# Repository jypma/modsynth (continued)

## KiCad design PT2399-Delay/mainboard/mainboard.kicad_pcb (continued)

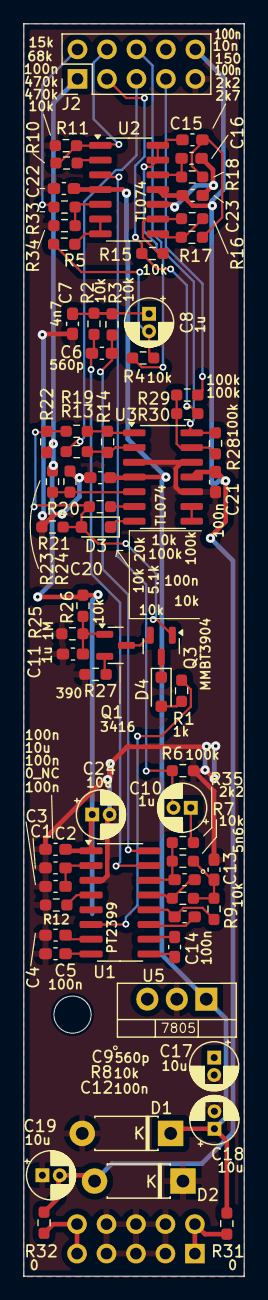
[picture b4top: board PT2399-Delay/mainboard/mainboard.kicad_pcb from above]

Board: 2 copper layers, 19.0 x 107.9 mm, 71 parts (1 on the bottom side), 51 nets.

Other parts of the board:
R6: 100k; R_0603_1608Metric_Pad0.98x0.95mm_HandSolder

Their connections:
/UNBUFFERED_WET: R6.1; also elsewhere on the board
GND: R6.2; also elsewhere on the board

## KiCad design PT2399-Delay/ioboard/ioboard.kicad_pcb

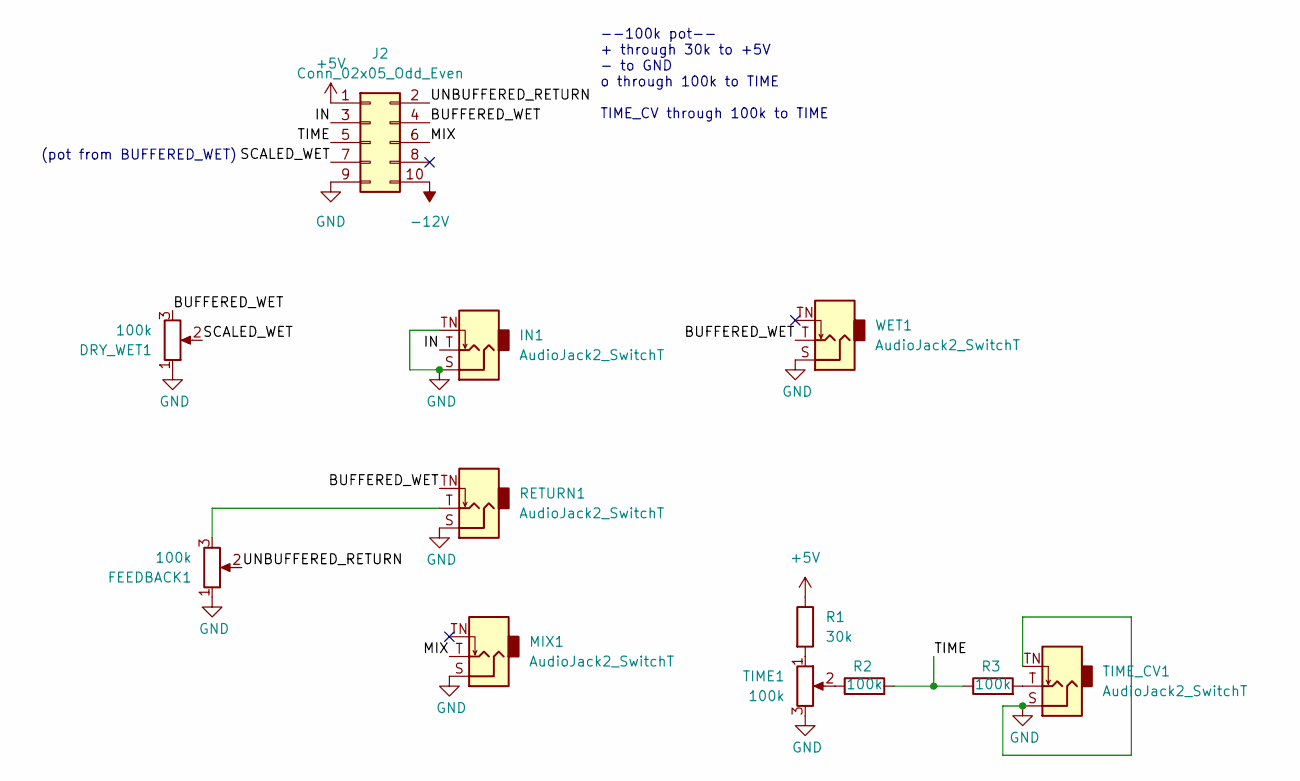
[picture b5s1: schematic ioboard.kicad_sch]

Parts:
DRY_WET1: 100k; Potentiometer_Alps_RK09K_Single_Vertical
FEEDBACK1: 100k; Potentiometer_Alps_RK09K_Single_Vertical
IN1: AudioJack2_SwitchT; Jack_3.5mm_QingPu_WQP-PJ398SM_Vertical_CircularHoles
J2: Conn_02x05_Odd_Even; PinHeader_2x05_P2.54mm_Vertical
MIX1: AudioJack2_SwitchT; Jack_3.5mm_QingPu_WQP-PJ398SM_Vertical_CircularHoles
R1: 30k; R_0603_1608Metric_Pad0.98x0.95mm_HandSolder
R2, R3: 100k; R_0603_1608Metric_Pad0.98x0.95mm_HandSolder
RETURN1: AudioJack2_SwitchT; Jack_3.5mm_QingPu_WQP-PJ398SM_Vertical_CircularHoles
TIME1: 100k; Potentiometer_Alps_RK09K_Single_Vertical
TIME_CV1: AudioJack2_SwitchT; Jack_3.5mm_QingPu_WQP-PJ398SM_Vertical_CircularHoles
WET1: AudioJack2_SwitchT; Jack_3.5mm_QingPu_WQP-PJ398SM_Vertical_CircularHoles

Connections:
+5V: J2.1, R1.1
-12V: J2.10
/BUFFERED_WET: DRY_WET1.3, J2.4, RETURN1.TN, WET1.T
/IN: IN1.T, J2.3
/MIX: J2.6, MIX1.T
/SCALED_WET: DRY_WET1.2, J2.7
/TIME: J2.5, R2.2, R3.1
/UNBUFFERED_RETURN: FEEDBACK1.2, J2.2
GND: DRY_WET1.1, FEEDBACK1.1, IN1.S, IN1.TN, J2.9, MIX1.S, RETURN1.S, TIME1.3, TIME_CV1.S, TIME_CV1.TN, WET1.S
unnamed: FEEDBACK1.3, RETURN1.T
unnamed: R1.2, TIME1.1
unnamed: R2.1, TIME1.2
unnamed: R3.2, TIME_CV1.T

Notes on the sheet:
(pot from BUFFERED_WET)
--100k pot-- + through 30k to +5V - to GND o through 100k to TIME TIME_CV through 100k to TIME

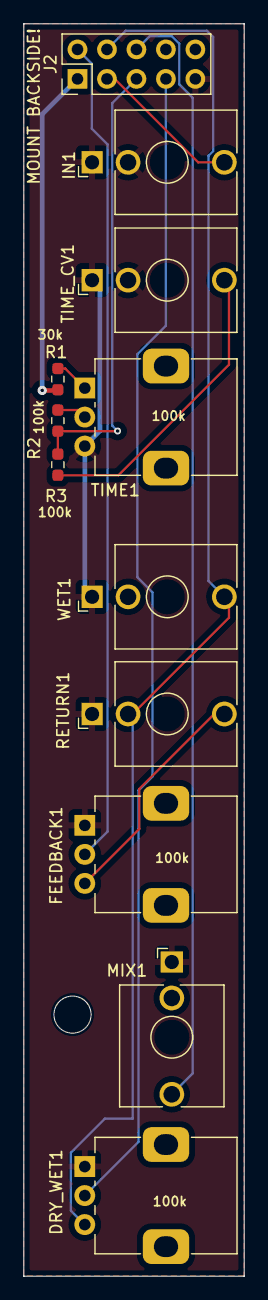
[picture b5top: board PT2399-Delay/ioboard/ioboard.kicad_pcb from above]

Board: 2 copper layers, 19.0 x 108.0 mm, 12 parts (0 on the bottom side), 12 nets.

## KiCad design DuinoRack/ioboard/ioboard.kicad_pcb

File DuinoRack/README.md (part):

# Design

- Screen
- 2 Encoders
- 2 bipolar CV inputs with Attenuverters and offset
  - On the MIDI variant, two attenuverters+offset are removed, to make space (only CV in for those).
CV inputs: attenuators plus offset, offset positive only
- 2 Gate inputs with trigger button.
- 2 CV outputs (from MPC4822, SPI)
- 2 Gate outputs (some I/O port)

# UI

Encoder 1: Select UI element
Encoder 2: Change value (immediate)

# Hardware
- Try a dual DIP/SOIC footprint for the ATMega328
- Run ATMega and MCP4822 off 5V, it'll be easier
- We might need a 5V precision reference for the ATMega's ADC (MCP4822 has internal reference)

## Notes for mainboard v1
- Remember: one TL074, one MCP6004!
- Zener diode is an inconvenient footprint. Just make it a normal zener THT.
- Value silkscreen is missing for C29 and C31 (both are 1 µF)
- Value silkscreen for ICs should be outside of the IC area
- No markings for power connector orientation
- Power connector is too close to the board edge
- MCP6004 isn't stable with the noise from the LEDs and screen. Add 2x 100nF (value needs to be tested) in parallel to R17 and R18.
- To reduce noise, C2 (AVCC cap for the ATMega) should be increased to 10uF (or perhaps in parallel to 100nF)
- C1 also to 10uF
- Replace the inrush resistors with links (test: 1Ohm ok?)
- 1k series resistors for OUTA (R10) and OUTB (R11) mess with the LEDs. Replace with 0k (see ioboard for replacement)
- In order for GATE OUT to reach -4V to +8V:
  + R49, R50 should be 15k (instead of 75k)
  + R47, R48 should be 20k (instead of 100k)
  + 2 extra 15k resistors from the common point of the above 2, to +5V (middle pin of the nearby voltage regulator), with modwire

## Notes for ioboard v1
- Value silkscreen is missing for R17, R18, R19 (should be 3.9k)
- Power and GND pins for screen are reversed, and should be cut and patched. Cause is that an earlier selected screen had these in reverse... From bottom view of  ioboard:
  - Rightmost screen pin should be VCC, scrape off solder mask of the actual VCC plane right below the pin, and blob connect.
  - Pin left of that should be GND, route to left button pin of rightmost encoder (still from bottom view of board). Unfortunately, the screen mislabeled GND pin was also the only route for GND to get onto the board. So, pin 15 of J4 (top right, bottom view) needs a jumper wire to that same GND encoder leg as well.
- GND plane wasn't regenerated properly. Use copper wire to connect several GND pins after assembly (see prototype). Combine with mod above.
- Attenuator pots are in reverse (bend pins 1 and 3 up, and swap with wires)
- LEDs for OUTA and OUTB should have 2k series resistor (THT) before going into GND hole.
- TODO Find a way to inject a 1k series resistor to the actual output jacks for OUTA and OUTB (might only be possible in next revision...)

# Software
- For high-detail modules (envelopes, LFO) try to update the MCP from a timer interrupt, so we can update the screen simultaneously? Perhaps only interrupt-driven WHILE we update the screen.
  - Otherwise, only update the screen after manual input, or on a low derivative...

# Potential modules

## ADSR

- 1 Gate input
- 4 variable inputs (can be virtual) for A,D,S,R (CV assignable)
   - positive only
   - not precise
- 1 CV output
- optional: 1 CV inverted output
- optional: 1 extra Gate input, 1 extra CV output (second envelope)

No looping (put LFO-like stuff in its own module)

Hints [here](https://github.com/baritonomarchetto/Programmable-Envelope-Generator/blob/main/ProgEnvGen_V2.ino)

## AR
(do we need this? Just have sustain at zero above)

- 1 Trigger input
- 2 CV inputs for A,D
- 1 CV output
- optional: 1 CV inverted output
- optional: 1 extra Gate input, 1 extra CV output (second envelope)

## LFO

- 1 input for tune (non-CV)
- 1 CV input (can be virtual) for freq
  - precise (if VCO frequency)
- optional: 1 Gate input for Freq.Counter / Tap tempo / Sync
- 1 menu input: Select wave shape
- 1 CV output
- optional: 1 CV output for extra wave, or 90 degrees offset wave
- toggle unipolar / bipolar

Hints [here](https://github.com/robertgallup/arduino-DualLFO). Need to check quality of the waveform using the MCP4822.

### To add:

- Offset, Attn (in addition to bidi? Instead of bidi?).
- Width (insert silence in middle of wave, where all waves are zero)
- Delay: Divide (2), Amount (%)... too complicated?
- Skip chance %
- EStep / ETrig (eucledean)
- Slop (earlier / later %,  but still in time?)

## LFO ADSR

Combine the two, applying the envelope to the LFO
- With reset on gate, or free-running
- Toggle unipolar / bipolar

## Pulse

- 1 input for tune (non-CV)
- 1 CV input (can be virtual) for freq
  - precise (if VCO frequency)
- optional: 1 Gate input for Freq.Counter / Tap Tempo / Sync
- 1 CV input (can be virtual): Pulse Width %
- 1 Gate output (or CV)
- optional: 3 extra outputs with dividers

## Clock divider

1 Gate input
N CV input + Gate output pairs, input sets divisor
Perhaps merge this with Pulse?

## Quantizer

Need to check if the incoming ADC is precise enough.

- 2 CV input
  - precise
- 2 Gate inputs for "hold"
- 2 CV outputs

## Sequencer

- encoder + 2 CV input for programming/recording. Modes for recording/setting CH1, CH2 or both
- Gate input advances the sequencer (consider internal clock as well)
- Add more later without adding UI elements

## MIDI

In:
- 2 CV outputs (note/bend and modulation)
- 1 Gate output
- 1 Clock output (selectable division)
- Selectable MIDI channel

Thru (electrical).

Out:
- 1 CV input (note & bend)
- 1 CV input (volume or mod)
- 1 Gate input
- Selectable MIDI channel
- Configurable to just send midi CV, no notes
- Configurable to mirror input (with 1-symbol delay), to allow chaining

Hints [here](https://note.com/solder_state/n/n17e028497eba) (incorporates pitch bend into the CV)
Original [midi2cv](https://github.com/elkayem/midi2cv)

## Random

- Noise with colors
- Random walk
- Sample & hold

## Chord quantizer mode

- Melody should pick different notes than just the chord

- Melody has fixed root note, scale is CV in, pitch is CV in

- Chord has root note (pitch) as CV in, chord type as CV in (scale is set to chromatic)
- Chord has 4 CV outputs
- Chord is stored as 16 bits (3x5 bit, for max 31 semitones offset).
- Use as mode for quantizer:
  + 2-channel note quantizer to one scale
  + 1-channel note quantizer with scale as CV-in
  + 1-channel chord quantizer with chord type as CV-in (selecting scale as chromatic, or anything that fits the sequencer before)

  Hence, for new Quantizer:
  - Mode: 2 notes, 1 note, chord
 - Clock input to sample and hold pitch, and rotate notes when in chord mode

 - Have quantizer create a gate when the pitch changes

# Simulation

## Output stage (TL074, -12..+12V)
[here](https://falstad.com/circuit/circuitjs.html?ctz=CQAgjCAMB0l3BWEBmATNA7AhAOBjVIAWfbEfc8ycgUwFowwAoIyAThADZUiVlOQGTjj4CIMAXTbQ2jMO2Q4wONpBxERMSKmTimAJS44RyYkZGoMqKDdbhr1R9AQHzKYW9aPb1Bg5swLoYIYNbICNZEaCgRNhB21v6BTADuXDwx1iFhsZBMAE5cCRlCFhnUofB5aaWigh6o5anpvGjU3LyNvNUtIF1F1P15hR19GRFl3SBEGPDNRGwC-RNj3UwA5tOLKGYLAsj8Aa574ES8J9vedkjeyQDy9SaHOHB1jgVbSxknYGc2pnNCid+idTFNCHMAPbgZBFWw4ThLJziFCo6iw5BMIA)
Try with 1% resistor and digital calibration, since it's far from the rails.

## Input stage (alt.2, MCP6004 protected, 0..5V)
- Not very useful, since pot controls offset, and needs to be in the middle for a bidirectional signal to make it through. Or is it? CV in would almost always be a
- Does the pot react the wrong way?
[here](https://falstad.com/circuit/circuitjs.html?ctz=CQAgjCAMB0l3BWEBmAHAJmgdgGzoRmACzICcpkORICkNNdCApgLRhgBQRkpIe1yZDhC5UKIeCjRhdGJHTIw8ZSvkh0HAEp9UY5JGo5d6rOijnu4M7KkItOvUYchuNupbbXzMO9oRgzZHR3IJRg8whLajdoOwB5ESdBYVQ4cRkoDgAnPnQBcP9A8LowVPhsvkt0PMSxaujwFQ4Ad1r1GtF0zNaqOnrc6n7IFoH2wxqg2RH+cBw6GaGOMCxqIiIxdjM1jdIzCFp4KXID1WUITSYAZwBLS4AXAEMAOwBjJntt8ACXdZBU7xcjABPgqCF2s3cVAhESaOTBZn6RFIwiGjWUH2RYxcmPwGXcdBYSBidgA5qNkAgzDMiGA8SN4ViFjVhq0GbT5jV2Zkcp9gmJeaYYeiyQKtrSTF5hgB7FyVCyoHDCJRSCB0ZAoczq5AcIA)
Build with 0.1% 100k and 180k resistors. Digital calibration after that.

## Input stage v2 (MCP6004, more accurate offset)
- Offset lands nicely in a middle range (maximum offset need not be calibrated)
- Calibrate 0V (offset to zero), and 4V (send precisely 4V on input)
[here](https://falstad.com/circuit/circuitjs.html?ctz=CQAgjCAMB0l3BWEBmAHAJmgdgGzoRmACzICcpkORICkNNdCApgLRhgBQRkpIOqqENzqpk6IXHBRoOKNMjpkYeCtUKQ6DgCUQWBOOT9d+lIbl1u4cXRvQE24+JLi9TquYkg2183YcJcFFRqIlJZNGo6CEsbX3sAeRBRJ0lUd2FzDgAnPgEg6gDw4LkwVBVs3UhqdDzkjTyo1Q4AdySxesE6jMgWyuq8-kEawR7WwY7cwQioXvH0dGo5ho4wLAKwcVXZBA2NBFkIZRV5SCQtJgBnAEsLgBcAQwA7AGMmf132cR3xMo9LJFiMHsORw+w0CxoNXBkXATR031M2xwdDEgM8LABcQ4AHNJkIwLJxkRfjZZmD5os8hSZjkEegsF9dsgzCjkPAKgjPjQPoEosgsOyAB4oKHoHhCUjIDS7ai7AAqAHsAA4AHQuAApIGqFQALAC2AEo1Tc1QAbBXNS63bUAMxtFyYtw4CqE4FkfNOI1gCH5WDA-P9oXQODC7tgcAgKJQcilyA4QA)

## Input stage v3 (offset now fixed, needs -9V)
[here](https://falstad.com/circuit/circuitjs.html?ctz=CQAgjCAMB0l3BWEBmAHAJmgdgGzoRmACzICcpkORICkNNdCApgLRhgBQRkpIOqqENzqpk6IXHBRoOKNMjpkYeCtUKQ6DgCUQWBOOT9d+lIbl1u4cXRvQE24+JLi9TquYkg2183YcJcFFRqIlJZNGo6CEsbX3sAeRBRJ0lUd2FzDgAnPgEg6gDw4LkwVBVs3UhqdDzkjTyo1Q4AdySxesE6jMgWyuq8-kEawR7WwY7cwQioXvH0dGo5ho4wLAKwcVXZBA2NBFkIZRV5SCQtJgBnAEsLgBcAQwA7AGMmf132cR3xMo8Yjxg9hyOH2GgWNBqYMi4DK8He4nQWC+ODoYliFjoLF46L8AHNJkIwLJxkRfjZZqD5os8lSZjlvuBdgytiVaHCAB4oSHoHhCUjIDS7ai7AAqAHsAA4AHQuAApIDKxQALAC2AEoZTcZQAbMXNS63RUAMyNFyYtw4YqE4FkUWQp0EWGgYDCyQCCAopH0Apg8AgqJQcgFyA4QA)

## Input stage v4 (offset now in the right direction, needs 8V)
[here](https://falstad.com/circuit/circuitjs.html?ctz=CQAgjCAMB0l3BWEBmAHAJmgdgGzoRmACzICcpkORICkNNdCApgLRhgBQRkpIOqqENzqpk6IXHBRoOKNMjpkYeCtUKQ6DgCUQWBOOT9d+lIbl1u4cXRvQE24+JLi9TquYkg2183YcIcOjRqIlJZYLkIS1kfGHsAeRBRJ0lUd2FzDgAnPgEUVGoEXHzqOnQsFWzdSGp0POSNPLplSoB3JLFGwQaMyA52itq8-kE6wT72ka7cwQiJmY10aimxqA4wLEKwcQ3ZBG2NAKkW+HlIJC0mAGcASyuAFwBDADsAYyZ-A-ZxffFUGzklhY4189hyOCO6CWNDqi1KGgq8E+4nKP0CKHQAIsWNBHAA5gsiGBZFMiP9MpNIdCVtC+gAPDGjHhCUjIDQHagHAAqAHsAA4AHSuAApIEKeQALAC2AEohXchQAbHmta73cUAMw1VyY936NC+B1+4GKfQJRVkGQtQk6Nn1ASCBRoxTmHB5QnAsmayHO3TOkAgQRQcjZyA4QA)

## -9V Reference
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
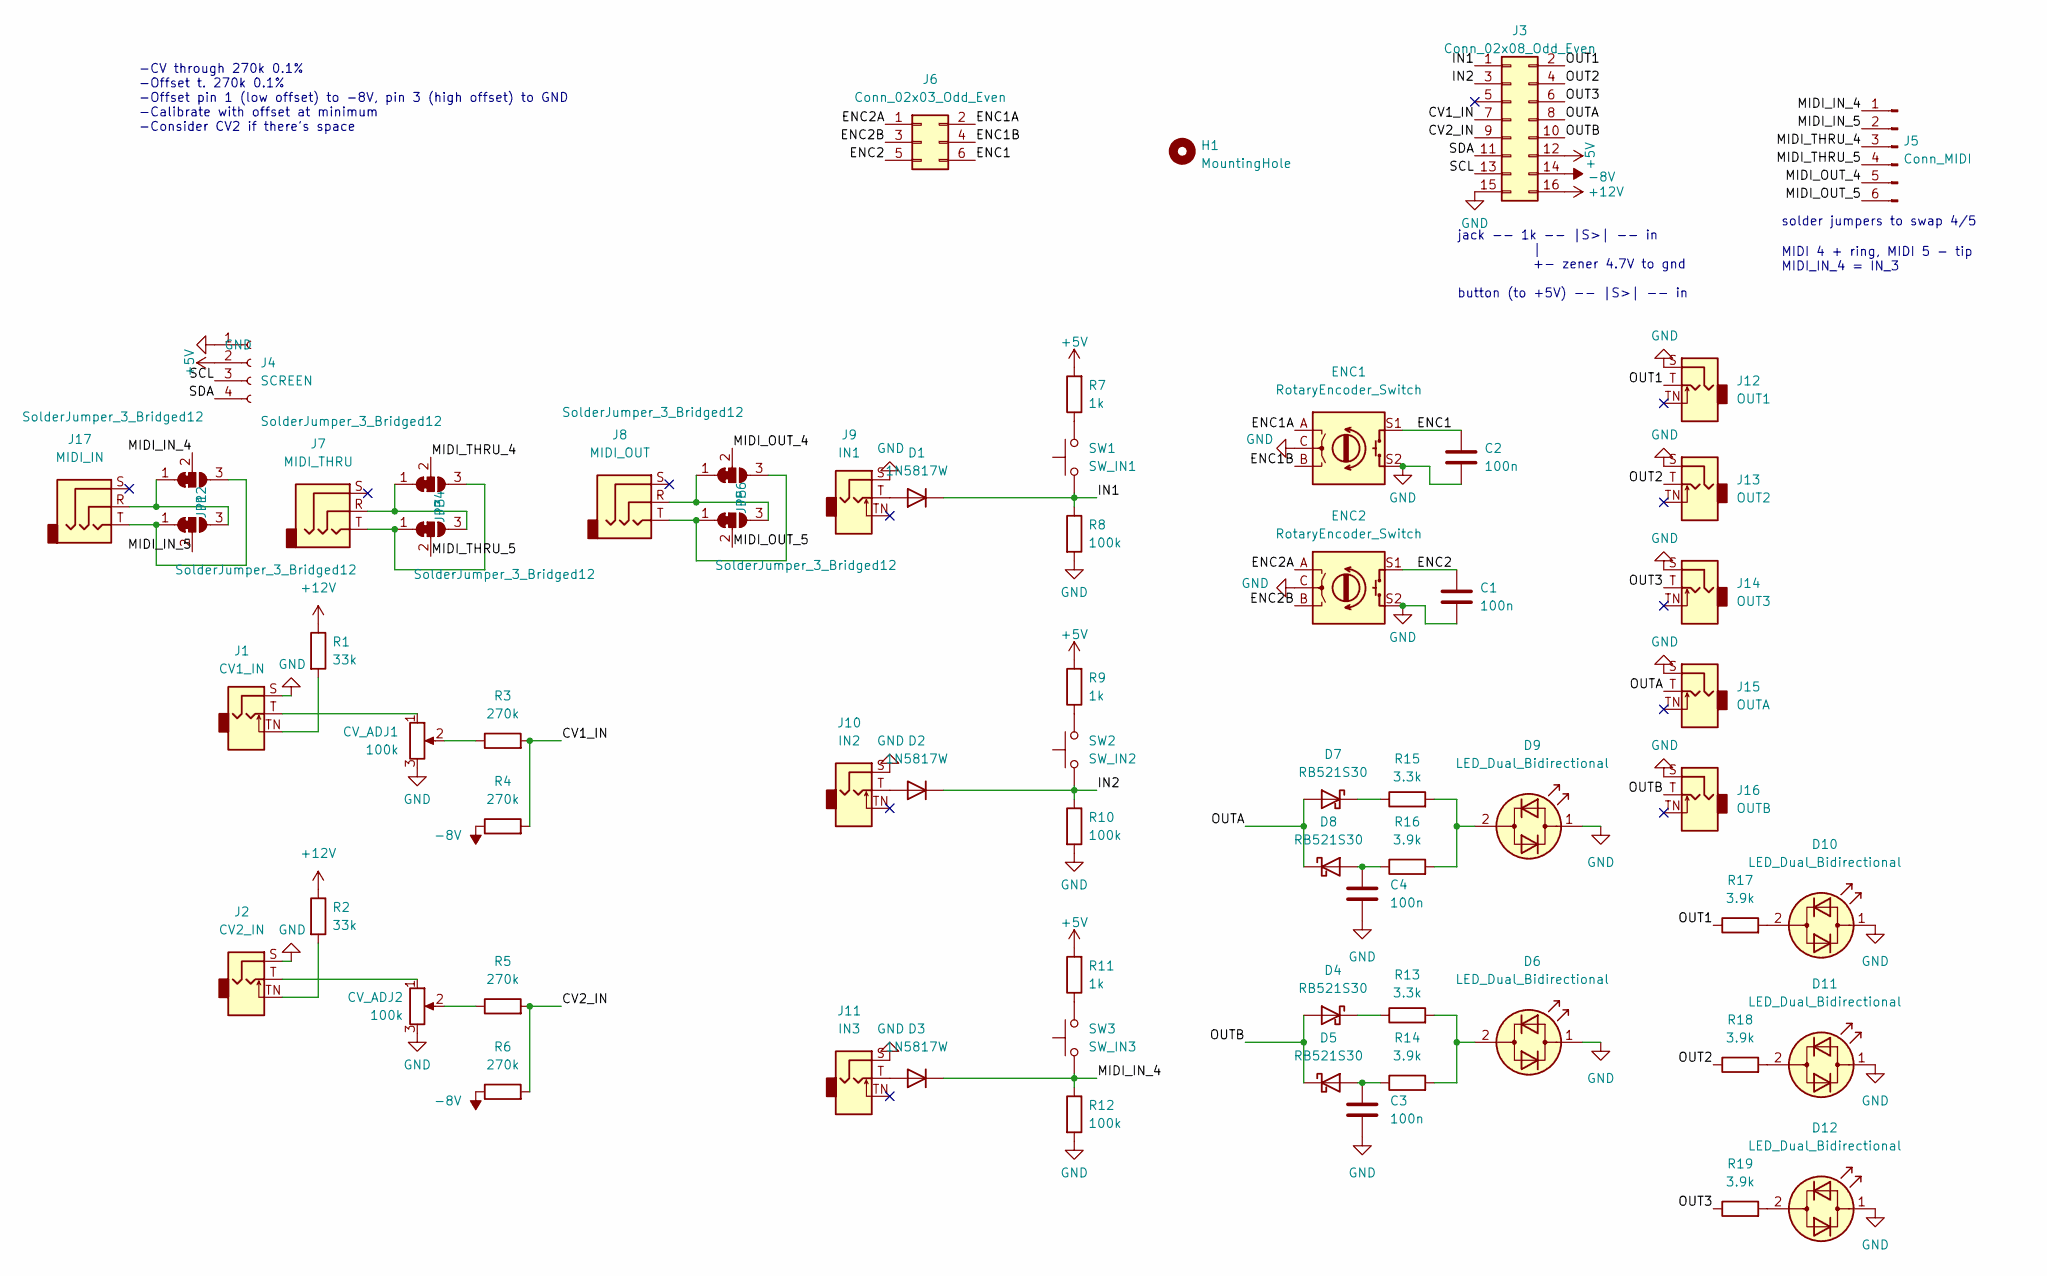
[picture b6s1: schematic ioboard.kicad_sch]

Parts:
C1, C2, C3, C4: 100n; C_0603_1608Metric_Pad1.08x0.95mm_HandSolder
CV_ADJ1, CV_ADJ2: 100k; Potentiometer_Alps_RK09K_Single_Vertical
D1, D2, D3: 1N5817W; D_SOD-123
D4, D5, D7, D8: RB521S30; D_SOD-523
D6, D9, D10, D11, D12: LED_Dual_Bidirectional; LED_D3.0mm
ENC1, ENC2: RotaryEncoder_Switch; RotaryEncoder_Alps_EC12E-Switch_Vertical_H20mm
H1: MountingHole; MountingHole_3.2mm_M3_DIN965
J1: CV1_IN; Jack_3.5mm_QingPu_WQP-PJ398SM_Vertical_CircularHoles
J2: CV2_IN; Jack_3.5mm_QingPu_WQP-PJ398SM_Vertical_CircularHoles
J3: Conn_02x08_Odd_Even; PinHeader_2x08_P2.54mm_Vertical
J4: SCREEN; PinSocket_1x04_P2.54mm_Vertical
J5: Conn_MIDI; PinHeader_1x06_P2.54mm_Vertical
J6: Conn_02x03_Odd_Even; PinHeader_2x03_P2.54mm_Vertical
J7: MIDI_THRU; Low-profile Minijack
J8: MIDI_OUT; Low-profile Minijack
J9: IN1; Jack_3.5mm_QingPu_WQP-PJ398SM_Vertical_CircularHoles
J10: IN2; Jack_3.5mm_QingPu_WQP-PJ398SM_Vertical_CircularHoles
J11: IN3; Jack_3.5mm_QingPu_WQP-PJ398SM_Vertical_CircularHoles
J12: OUT1; Jack_3.5mm_QingPu_WQP-PJ398SM_Vertical_CircularHoles
J13: OUT2; Jack_3.5mm_QingPu_WQP-PJ398SM_Vertical_CircularHoles
J14: OUT3; Jack_3.5mm_QingPu_WQP-PJ398SM_Vertical_CircularHoles
J15: OUTA; Jack_3.5mm_QingPu_WQP-PJ398SM_Vertical_CircularHoles
J16: OUTB; Jack_3.5mm_QingPu_WQP-PJ398SM_Vertical_CircularHoles
J17: MIDI_IN; Low-profile Minijack
JP1: SolderJumper_3_Bridged12
JP2, JP3, JP4, JP5, JP6: SolderJumper_3_Bridged12; SolderJumper-3_P1.3mm_Bridged12_RoundedPad1.0x1.5mm_NumberL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
R1, R2: 33k; R_0603_1608Metric_Pad0.98x0.95mm_HandSolder
R3, R4, R5, R6: 270k; R_0603_1608Metric_Pad0.98x0.95mm_HandSolder
R7, R9, R11: 1k; R_0603_1608Metric_Pad0.98x0.95mm_HandSolder
R8, R10, R12: 100k; R_0603_1608Metric_Pad0.98x0.95mm_HandSolder
R13, R15: 3.3k; R_0603_1608Metric_Pad0.98x0.95mm_HandSolder
R14, R16, R17, R18, R19: 3.9k; R_0603_1608Metric_Pad0.98x0.95mm_HandSolder
SW1: SW_IN1; SW_PUSH_6mm_H13mm
SW2: SW_IN2; SW_PUSH_6mm_H13mm
SW3: SW_IN3; SW_PUSH_6mm_H13mm

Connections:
+5V: J3.12, J4.2, R7.2, R9.2, R11.2
+12V: J3.16, R1.1, R2.1
-8V: J3.14, R4.1, R6.1
/CV1_IN: J3.7, R3.2, R4.2
/CV2_IN: J3.9, R5.2, R6.2
/ENC1: C2.1, ENC1.S1, J6.6
/ENC1A: ENC1.A, J6.2
/ENC1B: ENC1.B, J6.4
/ENC2: C1.1, ENC2.S1, J6.5
/ENC2A: ENC2.A, J6.1
/ENC2B: ENC2.B, J6.3
/IN1: D1.1 (K), J3.1, R8.1, SW1.1
/IN2: D2.1 (K), J3.3, R10.1, SW2.1
/MIDI_IN_4: D3.1 (K), J5.1, JP1.2 (C), R12.1, SW3.1
/MIDI_IN_5: J5.2, JP2.2 (C)
/MIDI_OUT_4: J5.5, JP5.2 (C)
/MIDI_OUT_5: J5.6, JP6.2 (C)
/MIDI_THRU_4: J5.3, JP3.2 (C)
/MIDI_THRU_5: J5.4, JP4.2 (C)
/OUT1: J3.2, J12.T, R17.1
/OUT2: J3.4, J13.T, R18.1
/OUT3: J3.6, J14.T, R19.1
/OUTA: D7.2 (A), D8.1 (K), J3.8, J15.T
/OUTB: D4.2 (A), D5.1 (K), J3.10, J16.T
/SCL: J3.13, J4.3
/SDA: J3.11, J4.4
GND: C1.2, C2.2, C3.2, C4.2, CV_ADJ1.3, CV_ADJ2.3, D6.1 (KA), D9.1 (KA), D10.1 (KA), D11.1 (KA), D12.1 (KA), ENC1.C, ENC1.S2, ENC2.C, ENC2.S2, J1.S, J2.S, J3.15, J4.1, J9.S, J10.S, J11.S, J12.S, J13.S, J14.S, J15.S, J16.S, R8.2, R10.2, R12.2
unnamed: C3.1, D5.2 (A), R14.1
unnamed: C4.1, D8.2 (A), R16.1
unnamed: CV_ADJ1.1, J1.T
unnamed: CV_ADJ1.2, R3.1
unnamed: CV_ADJ2.1, J2.T
unnamed: CV_ADJ2.2, R5.1
unnamed: D1.2 (A), J9.T
unnamed: D2.2 (A), J10.T
unnamed: D3.2 (A), J11.T
unnamed: D4.1 (K), R13.1
unnamed: D6.2 (AK), R13.2, R14.2
unnamed: D7.1 (K), R15.1
unnamed: D9.2 (AK), R15.2, R16.2
unnamed: D10.2 (AK), R17.2
unnamed: D11.2 (AK), R18.2
unnamed: D12.2 (AK), R19.2
unnamed: J1.TN, R1.2
unnamed: J2.TN, R2.2
unnamed: J7.R, JP3.1 (A), JP4.3 (B)
unnamed: J7.T, JP3.3 (B), JP4.1 (A)
unnamed: J8.R, JP5.1 (A), JP6.3 (B)
unnamed: J8.T, JP5.3 (B), JP6.1 (A)
unnamed: J17.R, JP1.1 (A), JP2.3 (B)
unnamed: J17.T, JP1.3 (B), JP2.1 (A)
unnamed: R7.1, SW1.2
unnamed: R9.1, SW2.2
unnamed: R11.1, SW3.2

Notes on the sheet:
solder jumpers to swap 4/5
jack -- 1k -- |S>| -- in | +- zener 4.7V to gnd button (to +5V) -- |S>| -- in
-CV through 270k 0.1% -Offset t. 270k 0.1% -Offset pin 1 (low offset) to -8V, pin 3 (high offset) to GND -Calibrate with offset at minimum -Consider CV2 if there's space
MIDI 4 + ring, MIDI 5 - tip MIDI_IN_4 = IN_3

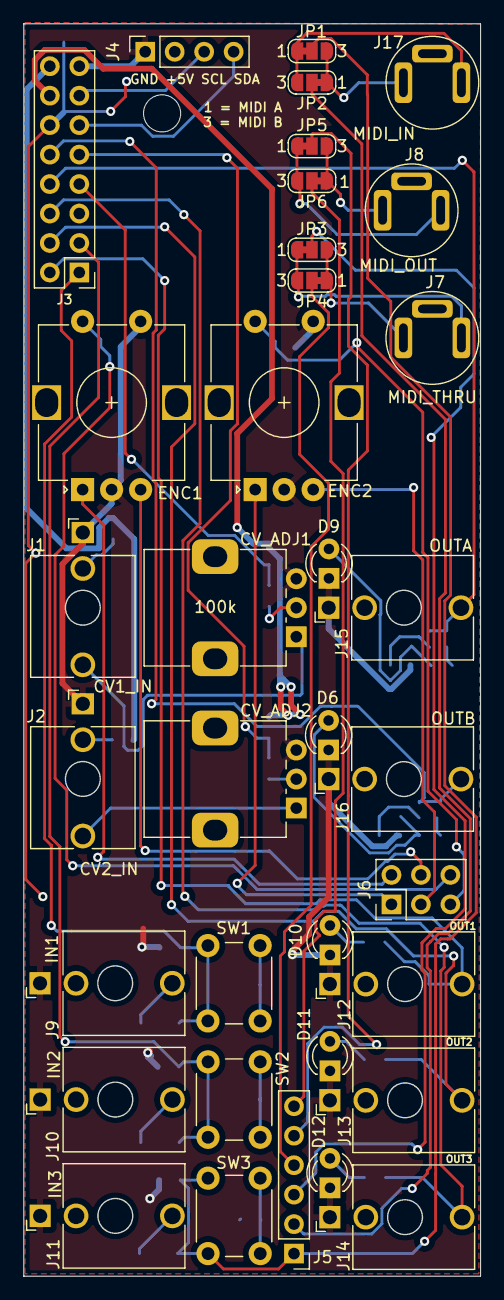
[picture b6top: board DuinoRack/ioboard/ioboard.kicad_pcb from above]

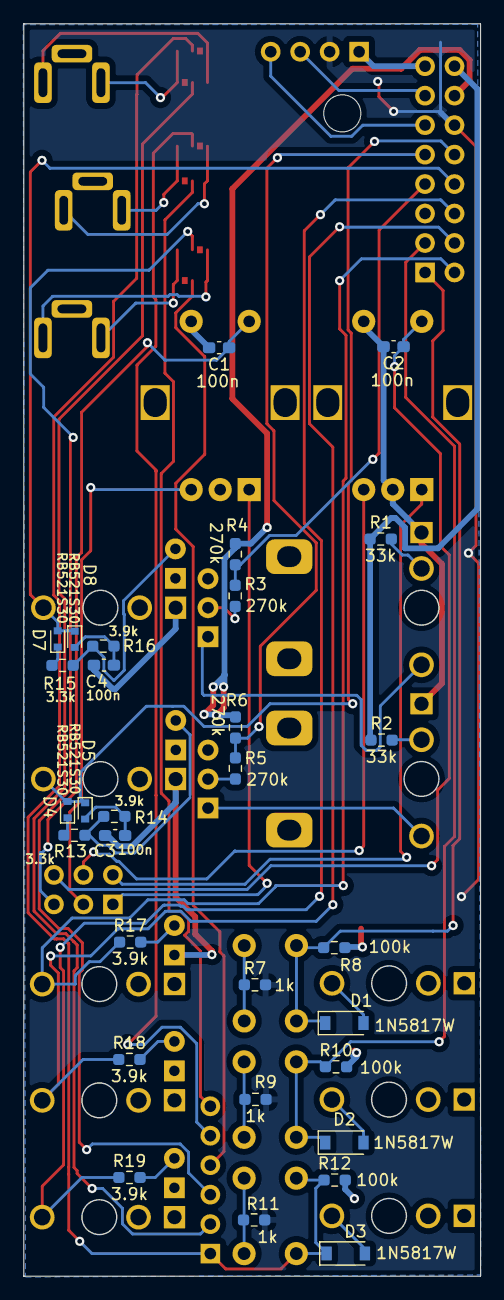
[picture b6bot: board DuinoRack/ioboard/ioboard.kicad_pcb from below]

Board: 2 copper layers, 39.4 x 107.9 mm, 66 parts (30 on the bottom side), 54 nets.

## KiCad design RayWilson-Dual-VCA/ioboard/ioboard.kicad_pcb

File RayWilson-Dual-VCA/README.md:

# Ray Wilson Dual VCA

Source: [RayWilson-Dual-VCA](https://github.com/gerb-ster/RayWilson-Dual-VCA/) on Github

The following modifications were made by me:

- Converted schematics and board to Kicad
- Added component values to silk screen
- Added a PCB faceplate in Kicad
- Split up into separate main and io board

## Main board

### Schematic

### PCB

## IO board

### Schematic

### PCB

## Face plate

# Calibration

See also the original instructions [here](http://musicfromouterspace.com/index.php?MAINTAB=SYNTHDIY&VPW=1910&VPH=716)

TODO: Look up the right R designations here

    Disconnect any inputs or CV from the VCA.
    Set the Log/Linear switch to Linear.
    Connect the black lead of a DVM set to volt range to ground.
    Connect the red lead of a DVM set to volt range to the wiper of BIAS control on panel.
    Adjust BIAS until you are as close as possible to 0 volts on the wiper.
    Disconnect the red lead.
    Connect the red lead of a DVM set to millivolt range to the output of the VCA.
    Adjust trimmer R1/R2 (100k) so that you have 0 volts on the output of the VCA.
    Disconnect the meter.
    Connect a 100 hz +/-5 volt square wave output from a signal generator to one of the CV inputs of the VCA.
    Observe the output of the VCA with an oscilloscope (adjust the scope as needed).
    The control voltage should appear on the output but at a much lower amplitude.
    Adjust trimmer R3/R4 (2k) to minimize the control voltage feedthrough.
       -> There's a balance here: If you do minimize the feedthrough, the VCA's max output level will be significantly attenuated (with a +5V signal). I leave it such that I still have ~80% of incoming oscillator signals left.
    If you have no oscilloscope you can listen to the output and adjust for least CV feedthrough.

# TODO

- Values are missing on I/O and main board
- IC value can't be read on main board
- No mounting holes in main and I/O board (there's space in the bottom for manual drilling)
- Holes for switches on I/O board aren't big enough. Drill is possible, but use lots of solder for channel2, since traces connect at the top (and drilling ruins the through-hole connection).
- SMD footprints are missing pin 1 circle

# Simulation

https://www.falstad.com/circuit/circuitjs.html?ctz=CQAgjCAMB0l3BWcMBMcUHYMGZIA4UA2ATmIxAUgoqoQFMBaMMAKACUQU89xiVOUAFl78qENJ2hIUUqFCktBkYiAwJ+2dSDyCem-hBiE5MSCmxh4V62c4sA7qq3ZsxjBJfHI7bXBDYJPD8uHioqJXBREwUOIKpsHV9wsC85CKYosIUAJyd+FARjHR4C1LQ4BzzOQqrPKEri6qLdfy1vXLV+QUJhPACQbuEqcvaqwZBCdwGeuUsrH0mumcWB-rCBsUz5BBYAc21+8b6u4lTvR07-Qh5L8e8OSwiUIWQnmvX0sC2YHYfIGsulgBEg+mxM20UyhApAMfGQ3BE4HkxiYP0gYE0CAQGLwCAwfSQpnMhhYuRh4AwzR4YEpchGDRapW0LRpXlJ0LhzAM+GpX1m1kq5K5HIMtPO8OpnJ54D54vJaB45NwQz2yCmyrVGlcJh8xD5Gr1+SmoMi4J+7KVkGEhv8Vv58zJcI1lnVdvCGHFlgRYE5KBSiNGX39PoMfuMITkuHg7KD4e9Yf8iWG8weCYSwljA39JoyZoUSm5L0INWY2uLxkMAB0AM6QGtKGsMYg1uu1luyVuthvV5ttvs-KA1sCNjDQQRkbCCbFW5SQDDdduUSnMQgoUgF1eCIdwGsAEzoADMAIYAVwANgAXQfV4fVhho5cpNfEDdCRdzzTXSDF7iFUjb1t92Pc8r1bW9OykD9CiCH9cRIXs5j3Q9T0va9bwYPBYCEPA9TIQpNHRcCxzwSk8B6BBiASK1nitACkOA1CwMbTD0UEfFXDxMAKMIDF23HIEKO-a5sDUXE6OrICUNAxsiN0UiwEEDEvkIXAFMbGA5MEIgeK+BJrhwQhxMkkDryYFt1OI+dtK5PSSNcIzkJM1szJvQhYHHDAXzgMAdC4Yg8AsuTrgUpSiFUrcbx3CTHMYmS+L1f58DxfA+BXQLiDnU5IHTNi+gIQzIsAmLpLvcD0sywhsp0XKEiIByGJKly3JIsw8BpXQLFwMiEHSoEko9HC-RSeqpLQ8za0srSuKCIRThwHrCvo0amLvDSSMmFTKIQLTBEU+c+JIqaEBm8dJk0EanKHRtiGgGlMBwWrNCwXQDspSlsC2na9oixDooasb+1gdEehXdFSACLgKJQC7Ypvcb7yBu6CBIx50UxOrFr+qTKi5WhdplCQI09L5hnjf0iZYESxBJih8dxiYXkMeoOAMhnhHLNnZltWg8x2DoyxeY5ObEAV2oOfhN3F1QJHEeBthANg6GrABLasLyPAA7ABjOh2SF9wqCFtrUi47x9iN-0jZaMIGR4FZGkl8UHcF-pHZxsx2cFlo3f2Swi29D3pfWYmyxLDE3DaGNw6qIEI6iNiU1eMRKqTyJQjSMFg5yGVtUBcx+Eud1o19-OY9L-EhnqXJSzjnOqTpGwWDF2PmWpOd+BtCA5jlgdFZVtXNZ1nwW8aEfswz00s9+ZAak7-5jBfSvwioXMp-dqZuGp7VN-qRwa+0II69b+olE2ZYSwCO2SwB1FoFxP0uB6BJKHD98PZ5EIfUECwYZK9DmGgPoVwxB1BnQVO2HipxLCkGOFgdQv9wA4yIOzMOoc2QPEvhMCIGIuATHwOCbB3wFB70wSsBS+CViBiUHbKY5CbhtAGB6e44BqEx1YRXAhK9ZTRD5iwihtDKDs2NMgCoAB5cAgiJgCLLMI7w4jGhMh3kyG2Ys6gKWEHUIQYgaA9yBkgAAwgANUqPoREEYQz1H2JoiImjZHskUhWfGDj-DahFvMRwainHBnxqMZxmiER1DccXTgATtQRlcOncUfjtTOLuPY-04wmR3BEdGMWWiszhgiNiAwKT5BoGwCAAAQsrI81YfDpOcek9MnDJ48PKVkvk6TtpLw2CAVedSLgeBif6QJLBxF+09hmQOeIzh9MiMGX0wYU42wAPZyBmAUr4a5hhSA+t-Y6kM4CVRUKYbydJVDkG8HMlwWDZjPBwvIeAhggasREh6VwXogx+iRFqfwLA5k8VOcvfy1AYDiEQXM2kMxNjLMuclOcc4PTmBIJ5LwNyICLJYEAA

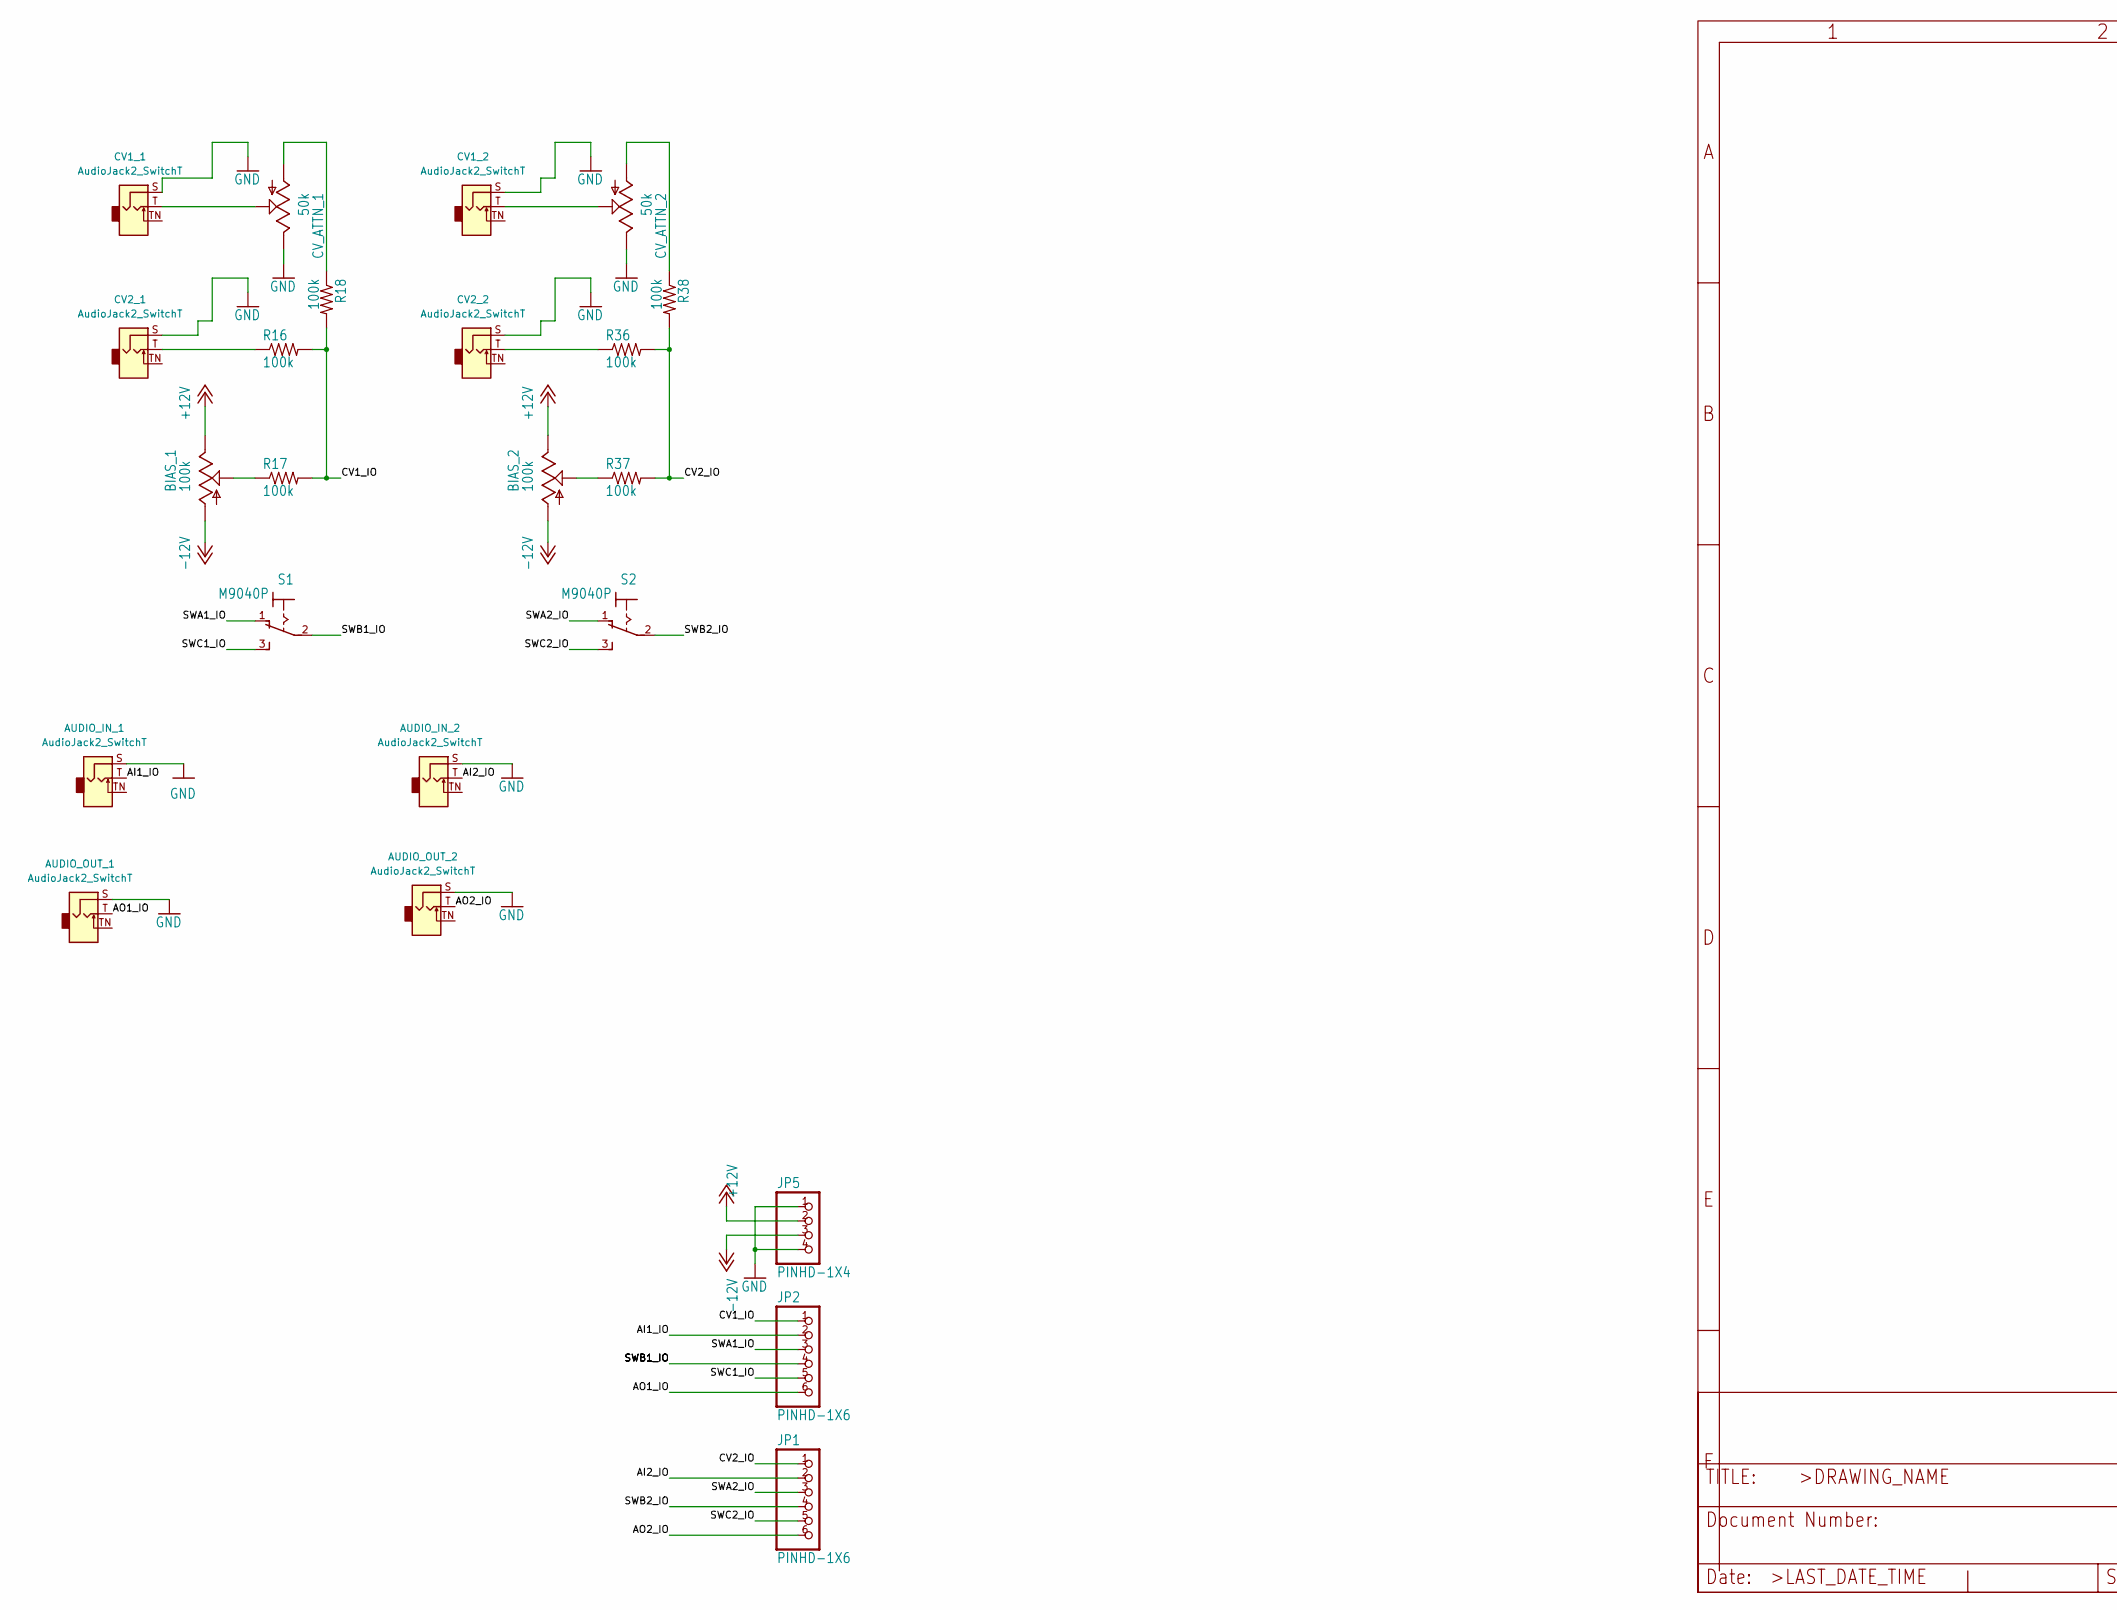
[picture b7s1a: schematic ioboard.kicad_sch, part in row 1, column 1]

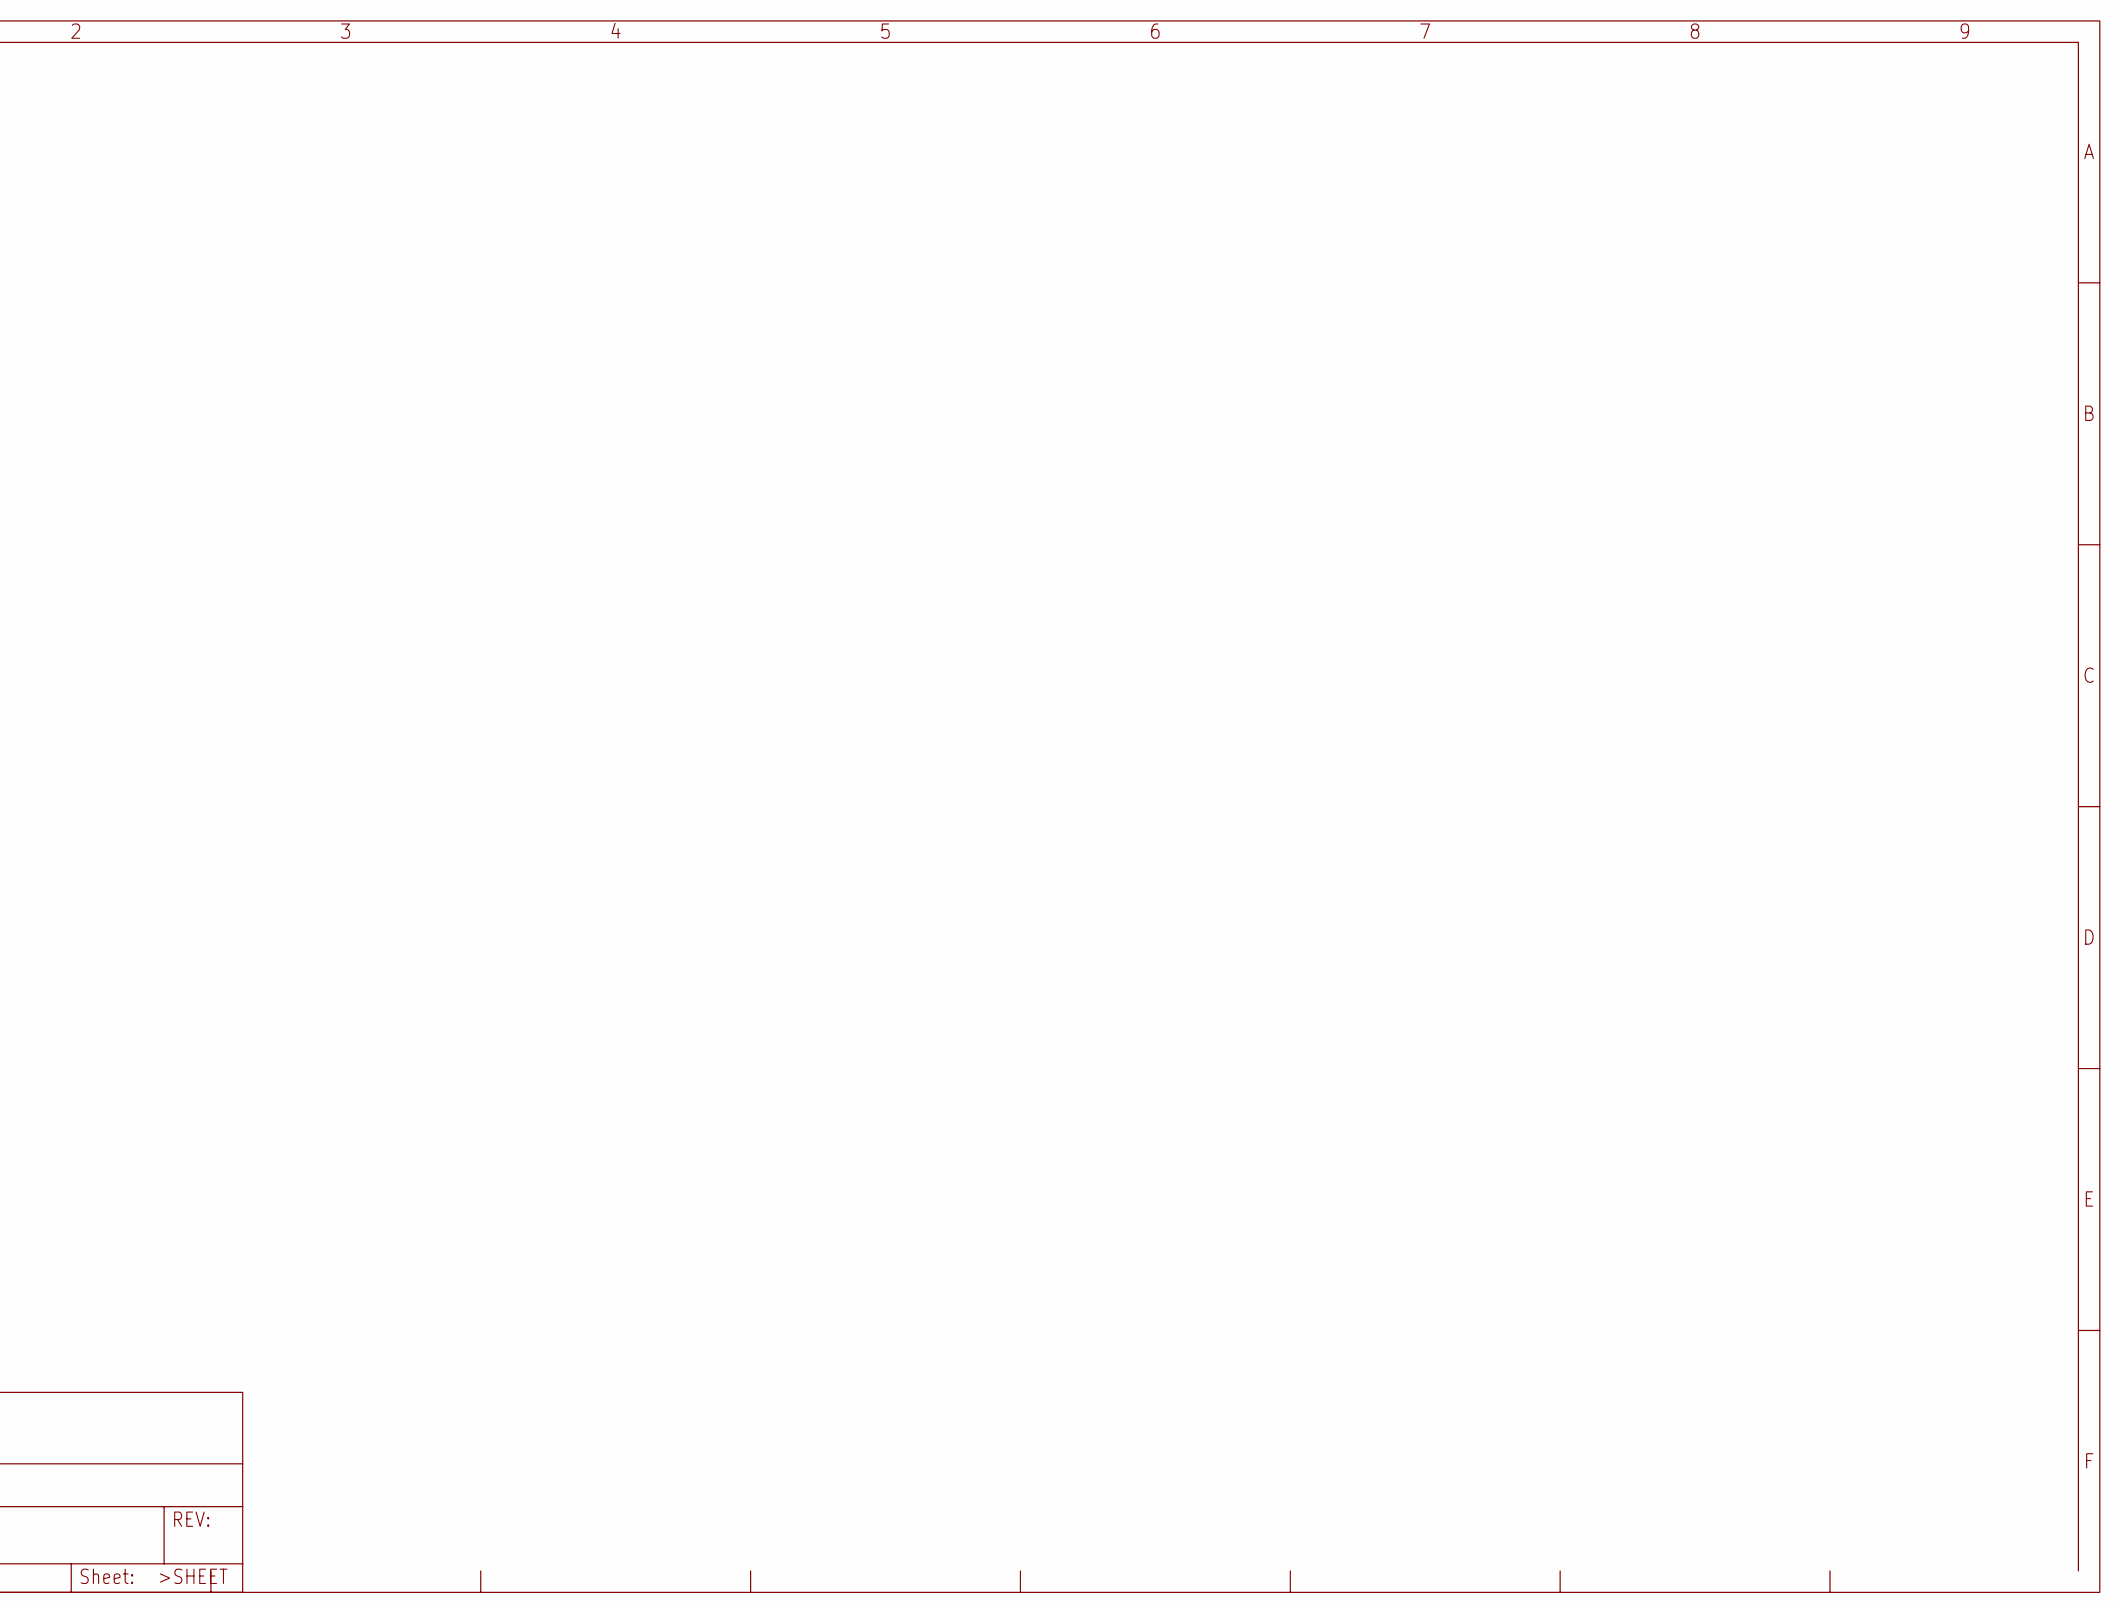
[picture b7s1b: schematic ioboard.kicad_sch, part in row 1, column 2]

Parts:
AUDIO_IN_1, AUDIO_IN_2: AudioJack2_SwitchT; Jack_3.5mm_QingPu_WQP-PJ398SM_Vertical_CircularHoles
AUDIO_OUT_1, AUDIO_OUT_2: AudioJack2_SwitchT; Jack_3.5mm_QingPu_WQP-PJ398SM_Vertical_CircularHoles
BIAS_1, BIAS_2: 100k; EVUF
CV1_1, CV1_2, CV2_1, CV2_2: AudioJack2_SwitchT; Jack_3.5mm_QingPu_WQP-PJ398SM_Vertical_CircularHoles
CV_ATTN_1, CV_ATTN_2: 50k; EVUF
JP1, JP2: PINHD-1X6; 1X06
JP5: PINHD-1X4; 1X04
R16, R17, R18, R36, R37, R38: 100k; 0204_7
S1, S2: M9040P

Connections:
+12V: BIAS_1.3 (E), BIAS_2.3 (E), JP5.2
-12V: BIAS_1.1 (A), BIAS_2.1 (A), JP5.3
/AI1_IO: AUDIO_IN_1.T, JP2.2
/AI2_IO: AUDIO_IN_2.T, JP1.2
/AO1_IO: AUDIO_OUT_1.T, JP2.6
/AO2_IO: AUDIO_OUT_2.T, JP1.6
/CV1_IO: JP2.1, R16.2, R17.2, R18.2
/CV2_IO: JP1.1, R36.2, R37.2, R38.2
/SWA1_IO: JP2.3, S1.1 (O)
/SWA2_IO: JP1.3, S2.1 (O)
/SWB1_IO: JP2.4, S1.2
/SWB2_IO: JP1.4, S2.2
/SWC1_IO: JP2.5, S1.3 (S)
/SWC2_IO: JP1.5, S2.3 (S)
GND: AUDIO_IN_1.S, AUDIO_IN_2.S, AUDIO_OUT_1.S, AUDIO_OUT_2.S, CV1_1.S, CV1_2.S, CV2_1.S, CV2_2.S, CV_ATTN_1.3 (E), CV_ATTN_2.3 (E), JP5.1, JP5.4
unnamed: BIAS_1.2 (S), R17.1
unnamed: BIAS_2.2 (S), R37.1
unnamed: CV1_1.T, CV_ATTN_1.2 (S)
unnamed: CV1_2.T, CV_ATTN_2.2 (S)
unnamed: CV2_1.T, R16.1
unnamed: CV2_2.T, R36.1
unnamed: CV_ATTN_1.1 (A), R18.1
unnamed: CV_ATTN_2.1 (A), R38.1

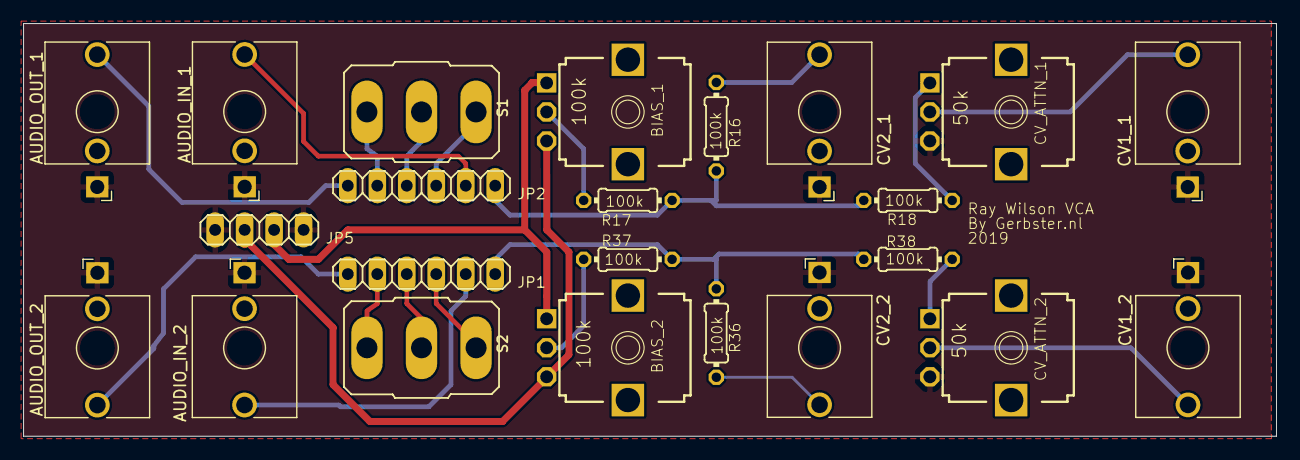
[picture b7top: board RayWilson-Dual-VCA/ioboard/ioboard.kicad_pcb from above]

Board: 2 copper layers, 108.0 x 35.6 mm, 23 parts (0 on the bottom side), 23 nets.
